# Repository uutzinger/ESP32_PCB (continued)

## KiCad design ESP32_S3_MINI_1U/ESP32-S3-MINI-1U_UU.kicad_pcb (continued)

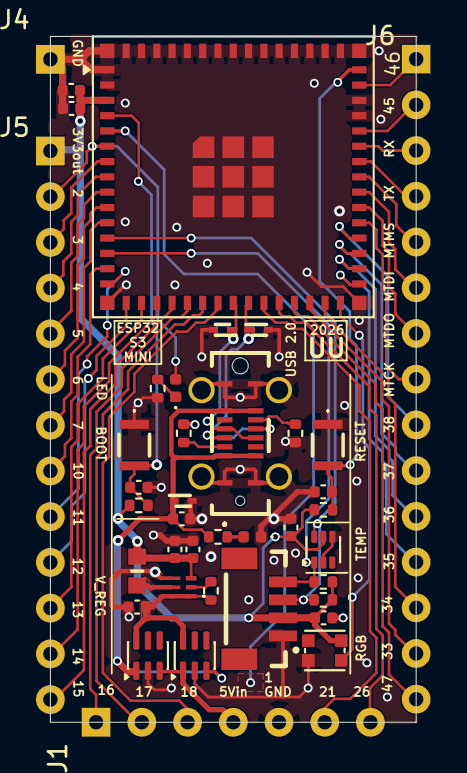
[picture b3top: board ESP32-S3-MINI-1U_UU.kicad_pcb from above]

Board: 2 copper layers, 20.3 x 38.1 mm, 39 parts (0 on the bottom side), 50 nets.

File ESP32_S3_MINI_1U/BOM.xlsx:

PCBWay BoM
Item # | *Designator | *Qty | Manufacturer | *Mfg Part # | Description / Value | Vendor Part # | *Package/Footprint | Category | Your Instructions / Notes | *Unit Price(5 sets) | *Total | *Delivery Time | *Actual Purchase Mfg Part # | *PCBWay Note | Customer Reply
1 | C11,C12,C10,C4 | 4 | muRata | GRM155R71A104KA01D | 0u1F | C71687 | C_0402_1005Metric | Capacitor | https://www.lcsc.com/product-detail/C71687.html?s_z=n_C71687 | 0.063 | 1.26
2 | C14 | 1 | YAGEO | CC0402KRX7R6BB103 | 10nF | C541371 | C_0402_1005Metric | Capacitor | https://www.lcsc.com/product-detail/C541371.html?s_z=n_C541371 | 0.126 | 0.63
3 | C3 | 1 | muRata | GRM158R61A226ME15D | 22uF | C3845593 | C_0402_1005Metric | Capacitor | https://www.lcsc.com/product-detail/C3845593.html?s_z=n_C3845593 | 0.263 | 1.315
4 | C5,C1,C2 | 3 | muRata | GRM155R61A106ME44D | 10uF | C77000 | C_0402_1005Metric | Capacitor | https://www.lcsc.com/product-detail/C77000.html?s_z=n_C77000 | 0.123 | 1.845
5 | C9 | 1 | muRata | GRM155R61A475KEAAD | 4u7F | C77004 | C_0402_1005Metric | Capacitor | https://www.lcsc.com/product-detail/C77004.html?s_z=n_C77004 | 0.158 | 0.79
6 | D1 | 1 | onSemi | ESD9B5.0ST5G | ESD9B5.0ST5G | C111566『 』863-ESD9B5.0ST5G | D_SOD-923 | V_USB ESD | https://www.lcsc.com/product-detail/C111566.html?s_z=n_C111566『 』https://www.mo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 | 0.212 | 1.06
7 | D4,D5 | 2 | Vishay | VLMB1500-GS08 | LED BLUE | C511042『 』78-VLMB1500-GS08 | LED_0402_1005Metric | LED | https://www.lcsc.com/product-detail/C511042.html?s_z=n_C511042『 』https://www.mo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 | 0.419 | 4.19
8 | D6 | 1 | Worldsemi | WS2812B-2020 | WS2812B | C965555 | WS2812_2020 | RGB LED | https://www.lcsc.com/product-detail/C965555.html?s_z=n_C965555 | 0.119 | 0.595
9 | D7,D8 | 2 | onSemi | ESD9101P2T5G | ESD9101P2T5G | C41348159『 』863-ESD9101P2T5G | D_SOD-923 | USB ESD | https://www.lcsc.com/product-detail/C41348159.html?s_z=n_ESD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 』https:/… | 0.066 | 0.66
10 | IC1 | 1 | Texas Instruments | TPS6282533DMQR | TPS6282533DMQR | C3189971『 』595-TPS6282533DMQR | TPS6282533DMQR | Volt Regulator | https://www.lcsc.com/product-detail/C3189971.html?s_z=n_C3189971『 』https://www.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 | 1.811 | 9.055
11 | J1 | 1 | Do No Populate | Do No Populate | Castellated_1x07 |  | Castellated_1x07_P2.54mm_D0.80mm | Connector |  |  |  |  |  | [DNP不要贴];
12 | J2 | 1 | GCT | USB4120-03-C | USB4120-03-C | C3445864『 』640-USB4120-03-C | USB412003C | Connector | https://www.lcsc.com/product-detail/C3445864.html?s_z=n_C3445864『 』https://www.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 | 1.642 | 8.21
13 | J3 | 1 | BOOMELE | 1.0T-4P | Qwiic_Vertical | C2974722 | JST_1x04_P1.0mm_Vertical_SMD | Connector | https://www.lcsc.com/product-detail/C2974722.html | 0.43 | 2.15 |  | 1.0T-4P卧贴编带
14 | J4 | 1 | Do No Populate | Do No Populate | Castellated_1x01 |  | Castellated_1x01_P2.54mm_D0.80mm | Connector |  |  |  |  |  | [DNP不要贴];
15 | J5 | 1 | Do No Populate | Do No Populate | Castellated_1x13 |  | Castellated_1x13_P2.54mm_D0.80mm | Connector |  |  |  |  |  | [DNP不要贴];
16 | J6 | 1 | Do No Populate | Do No Populate | Castellated_1x15 |  | Castellated_1x15_P2.54mm_D0.80mm | Connector |  |  |  |  |  | [DNP不要贴];
17 | L1 | 1 | TDK | TFM160808ALC-R47MTAA | TFM160808ALC-R47MTAA | C695609『 』810-TFM160808ALCR47A | INDC1608X75N | Inductor | https://www.lcsc.com/product-detail/C695609.html?s_z=n_C695609『 』https://www.mo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 | 0.357 | 1.785
18 | R1 | 1 | YAGEO | RC0402FR-07100KL | 100k | C60491 | R_0402_1005Metric | Resistor | https://www.lcsc.com/product-detail/C60491.html?s_z=n_C60491 | 0.032 | 0.16
19 | R12,R11 | 2 | YAGEO | RC0402FR-072K2L | 2k2 | C114762 | R_0402_1005Metric | Resistor | https://www.lcsc.com/product-detail/C114762.html?s_z=n_C114762 | 0.019 | 0.19
20 | R13,R17 | 2 | YAGEO | RC0402FR-0710KL | 10k | C60490 | R_0402_1005Metric | Resistor | https://www.lcsc.com/product-detail/C60490.html?s_z=n_C60490 | 0.019 | 0.19
21 | R14,R16 | 2 | YAGEO | RC0402FR-074K7L | 4k7 | C105871 | R_0402_1005Metric | Resistor | https://www.lcsc.com/product-detail/C105871.html?s_z=n_C105871 | 0.019 | 0.19
22 | R4,R5 | 2 | YAGEO | RC0402FR-075K1L | 5k1 | C105872 | R_0402_1005Metric | Resistor | https://www.lcsc.com/product-detail/C105872.html?s_z=n_C105872 | 0.019 | 0.19
23 | S1,S2 | 2 | C&K | NANOT160AS | NANOT160AS | C2760981『 』611-NANOT160AS | NANOT160AS | Micro Switch | https://www.lcsc.com/product-detail/C2760981.html?s_z=n_C2760981『 』https://www.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 | 0.686 | 6.86 | 7-10 Workdays
24 | U1 | 1 | Espressif Systems | ESP32-S3-MINI-1U-N8 | ESP32 S3 Mini 1U 8MB Flash | C2980299 | ESP32-S2-MINI-1U | MCU Module | https://www.lcsc.com/product-detail/C2980299.html?s_z=n_ESP3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 | 6.883 | 34.415 |  |  | The quoted part number is [ESP32-S3-MINI-1U-N8], not [ESP32-S2] as specified in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
25 | U2,U3 | 2 | Texas Instruments | LM66100DCK | Ideal Diode, Input Polarity Prot. | C2869734『 』595-LM66100DCKT | SOT-363_SC-70-6 | Ideal Diode | https://www.lcsc.com/product-detail/C2869734.html?s_z=n_C2869734『 』https://www.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 | 0.221 | 2.21
26 | U4 | 1 | Texas Instruments | TMP112AIDRLR | TMP112 | C28927 | SOT-563 | Temp Sensor | https://www.lcsc.com/product-image/C28927.html | 1.65 | 8.25
 |  |  |  |  |  |  |  |  |  | Component Cost | 86.2

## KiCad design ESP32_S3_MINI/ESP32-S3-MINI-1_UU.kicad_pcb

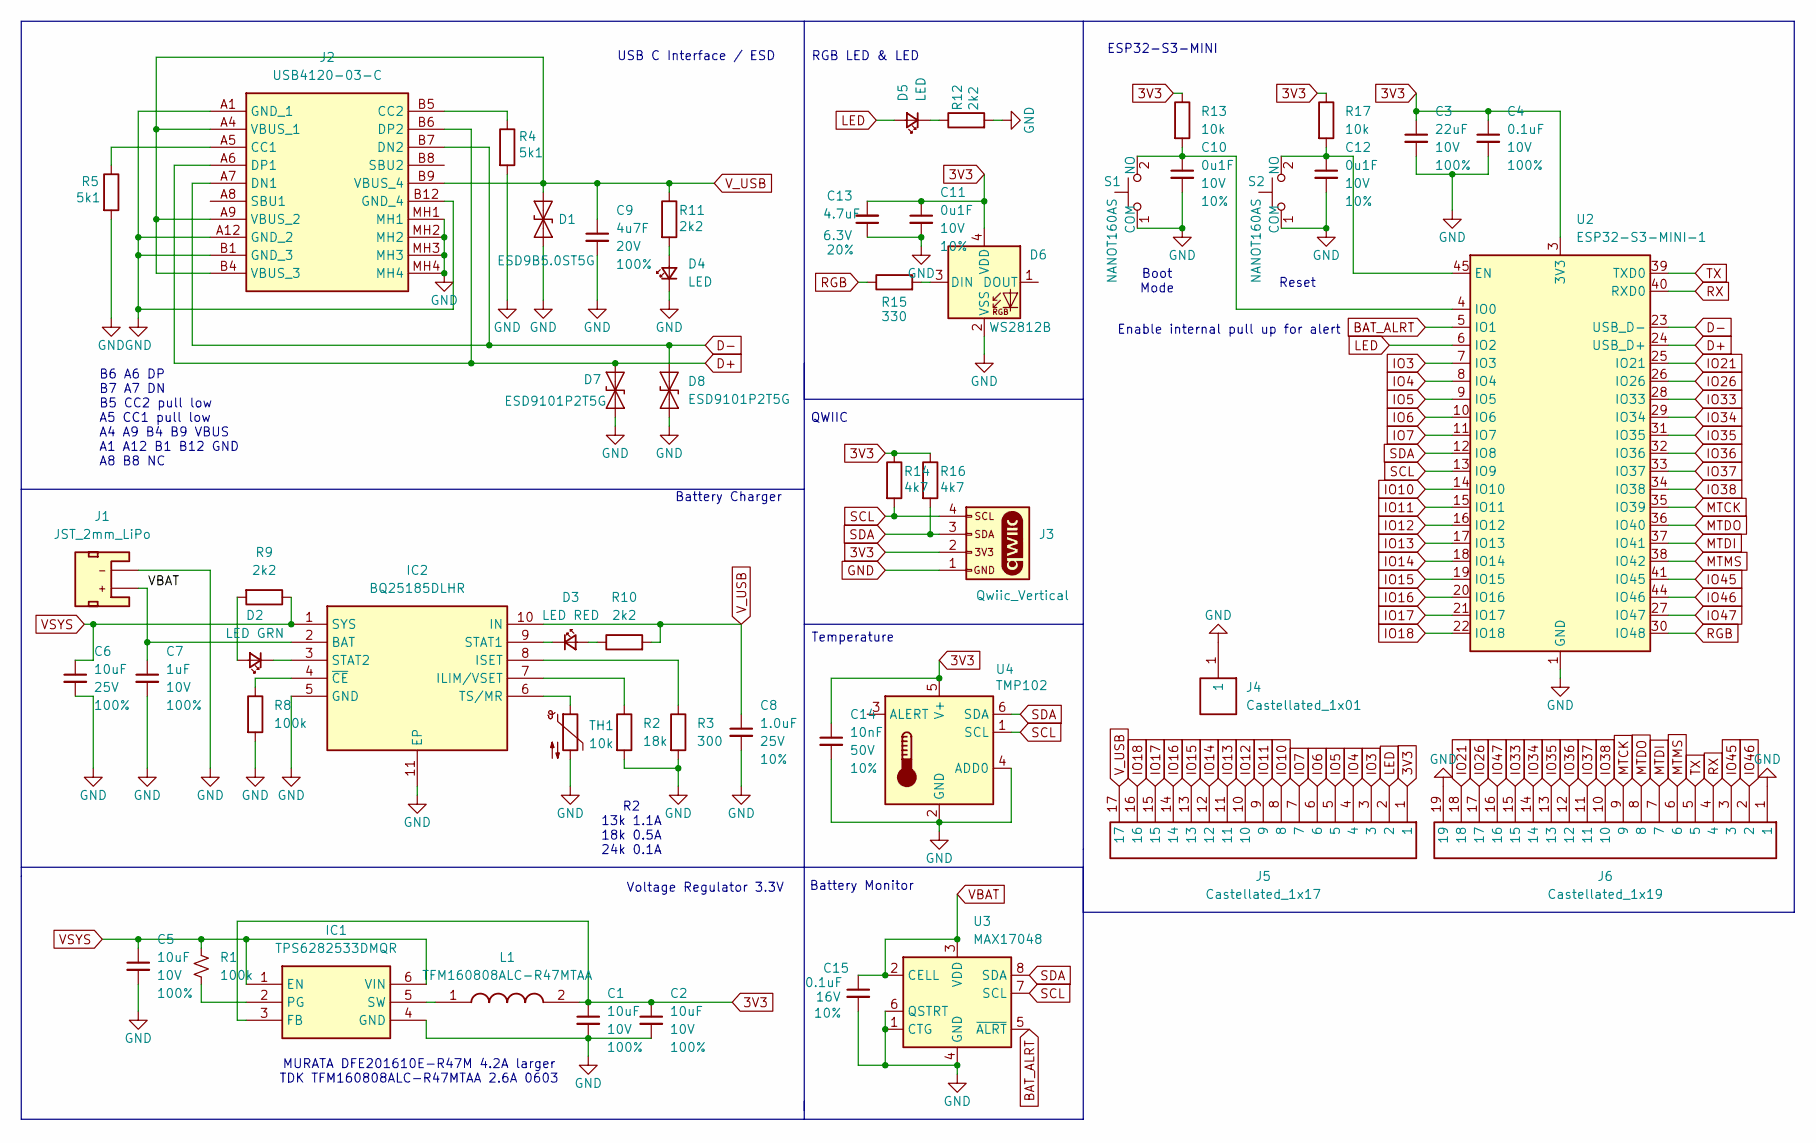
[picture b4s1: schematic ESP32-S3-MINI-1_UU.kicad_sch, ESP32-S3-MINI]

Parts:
C1, C2, C5: 10uF; C_0402_1005Metric; Voltage 10V; Tolerance 100%
C3: 22uF; C_0402_1005Metric; Voltage 10V; Tolerance 100%
C4: 0.1uF; C_0402_1005Metric; Voltage 10V; Tolerance 100%
C6: 10uF; C_0402_1005Metric; Voltage 25V; Tolerance 100%
C7: 1uF; C_0402_1005Metric; Voltage 10V; Tolerance 100%
C8: 1.0uF; C_0402_1005Metric; Voltage 25V; Tolerance 10%
C9: 4u7F; C_0402_1005Metric; Voltage 20V; Tolerance 100%
C10, C11, C12: 0u1F; C_0402_1005Metric; Voltage 10V; Tolerance 10%
C13: 4.7uF; C_0402_1005Metric; Voltage 6.3V; Tolerance 20%
C14: 10nF; C_0402_1005Metric; Voltage 50V; Tolerance 10%
C15: 0.1uF; C_0402_1005Metric; Voltage 16V; Tolerance 10%
D1: ESD9B5.0ST5G; D_SOD-923
D2: LED GRN; LED_0402_1005Metric
D3: LED RED; LED_0402_1005Metric
D4, D5: LED; LED_0402_1005Metric
D6: WS2812B; WS2812_2020
D7, D8: ESD9101P2T5G; D_SOD-923
IC1: TPS6282533DMQR; Manufacturer_Part_Number TPS6282533DMQR; Mouser Part Number 595-TPS6282533DMQR
IC2: BQ25185DLHR; SON40P220X200X80-11N; Manufacturer_Part_Number BQ25185DLHR; Mouser Part Number 595-BQ25185DLHR
J1: JST_2mm_LiPo; JST_1x02_P2.0mm_Horizontal_SMD
J2: USB4120-03-C; USB412003C; Manufacturer_Part_Number USB4120-03-C; Mouser Part Number 640-USB4120-03-C
J3: Qwiic_Vertical; JST_1x04_P1.0mm_Vertical_SMD
J4: Castellated_1x01; Castellated_1x01_P2.54mm_D0.80mm
J5: Castellated_1x17; Castellated_1x017_P2.54mm_D0.80mm
J6: Castellated_1x19; Castellated_1x019_P2.54mm_D0.80mm
L1: TFM160808ALC-R47MTAA; INDC1608X75N; Manufacturer_Part_Number TFM160808ALC-R47MTAA; Mouser Part Number 810-TFM160808ALCR47A
R1, R8: 100k; R_0402_1005Metric
R2: 18k; R_0402_1005Metric
R3: 300; R_0402_1005Metric
R4, R5: 5k1; R_0402_1005Metric
R9, R10, R11, R12: 2k2; R_0402_1005Metric
R13, R17: 10k; R_0402_1005Metric
R14, R16: 4k7; R_0402_1005Metric
R15: 330; R_0402_1005Metric
S1, S2: NANOT160AS; Mouser Part Number 611-NANOT160AS
TH1: 10k; R_0402_1005Metric
U2: ESP32-S3-MINI-1; ESP32-S2-MINI-1
U3: MAX17048; DFN-8_2x2mm_P0.5mm_EP1.2x0.8mm
U4: TMP102; SOT-563

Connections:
3V3: C1.1, C2.1, C3.1, C4.1, C11.1, C13.2, C14.1, D6.4 (VDD), IC1.3 (FB), J3.2, J5.1, L1.2, R13.1, R14.1, R16.1, R17.1, U2.3 (3V3), U4.5 (V+)
BAT_ALRT: U2.5 (IO1), U3.5 (~ALRT)
D+: D7.2 (A2), J2.A6 (DP1), J2.B6 (DP2), U2.24 (USB_D+)
D-: D8.2 (A2), J2.A7 (DN1), J2.B7 (DN2), U2.23 (USB_D-)
GND: C1.2, C2.2, C3.2, C4.2, C5.2, C6.2, C7.2, C8.2, C9.2, C10.2, C11.2, C12.2, C13.1, C14.2, C15.2, D1.1 (A1), D4.1 (K), D6.2 (VSS), D7.1 (A1), D8.1 (A1), IC1.4 (GND), IC2.5 (GND), IC2.11 (EP), J1.1 (-), J2.A1 (GND_1), J2.A12 (GND_2), J2.B1 (GND_3), J2.B12 (GND_4), J2.MH1, J2.MH2, J2.MH3, J2.MH4, J3.1, J4.1, J6.1, J6.19, R2.2, R3.2, R4.2, R5.2, R8.2, R12.2, S1.1 (COM), S2.1 (COM), TH1.2, U2.1 (GND), U2.2 (GND), U2.42 (GND), U2.43 (GND), U2.46 (GND), U2.47 (GND), U2.48 (GND), U2.49 (GND), U2.50 (GND), U2.51 (GND), U2.52 (GND), U2.53 (GND), U2.54 (GND), U2.55 (GND), U2.56 (GND), U2.57 (GND), U2.58 (GND), U2.59 (GND), U2.60 (GND), U2.61 (GND), U2.62 (GND), U2.63 (GND), U2.64 (GND), U2.65 (GND), U3.1 (CTG), U3.4 (GND), U3.6 (QSTRT), U3.9 (GND), U4.2 (GND), U4.4 (ADD0)
IO3: J5.3, U2.7 (IO3)
IO4: J5.4, U2.8 (IO4)
IO5: J5.5, U2.9 (IO5)
IO6: J5.6, U2.10 (IO6)
IO7: J5.7, U2.11 (IO7)
IO10: J5.8, U2.14 (IO10)
IO11: J5.9, U2.15 (IO11)
IO12: J5.10, U2.16 (IO12)
IO13: J5.11, U2.17 (IO13)
IO14: J5.12, U2.18 (IO14)
IO15: J5.13, U2.19 (IO15)
IO16: J5.14, U2.20 (IO16)
IO17: J5.15, U2.21 (IO17)
IO18: J5.16, U2.22 (IO18)
IO21: J6.18, U2.25 (IO21)
IO26: J6.17, U2.26 (IO26)
IO33: J6.15, U2.28 (IO33)
IO34: J6.14, U2.29 (IO34)
IO35: J6.13, U2.31 (IO35)
IO36: J6.12, U2.32 (IO36)
IO37: J6.11, U2.33 (IO37)
IO38: J6.10, U2.34 (IO38)
IO45: J6.3, U2.41 (IO45)
IO46: J6.2, U2.44 (IO46)
IO47: J6.16, U2.27 (IO47)
LED: D5.2 (A), J5.2, U2.6 (IO2)
MTCK: J6.9, U2.35 (IO39)
MTDI: J6.7, U2.37 (IO41)
MTDO: J6.8, U2.36 (IO40)
MTMS: J6.6, U2.38 (IO42)
unnamed: D2.2 (A), R9.2
unnamed: D2.1 (K), IC2.3 (STAT2)
unnamed: D3.2 (A), R10.1
unnamed: D3.1 (K), IC2.9 (STAT1)
unnamed: D4.2 (A), R11.2
unnamed: D5.1 (K), R12.1
unnamed: D6.3 (DIN), R15.2
unnamed: IC1.2 (PG), R1.1
unnamed: IC1.5 (SW), L1.1
unnamed: IC2.7 (ILIM/VSET), R2.1
unnamed: IC2.8 (ISET), R3.1
unnamed: IC2.6 (TS/MR), TH1.1
unnamed: IC2.4 (~CE), R8.1
unnamed: J2.A5 (CC1), R5.1
unnamed: J2.B5 (CC2), R4.1
unnamed: C10.1, R13.2, S1.2 (NO), U2.4 (IO0)
unnamed: C12.1, R17.2, S2.2 (NO), U2.45 (EN)
RGB: R15.1, U2.30 (IO48)
RX: J6.4, U2.40 (RXD0)
SCL: J3.4, R14.2, U2.13 (IO9), U3.7 (SCL), U4.1 (SCL)
SDA: J3.3, R16.2, U2.12 (IO8), U3.8 (SDA), U4.6 (SDA)
TX: J6.5, U2.39 (TXD0)
VBAT: C7.1, C15.1, IC2.2 (BAT), J1.2 (+), U3.2 (CELL), U3.3 (VDD)
VSYS: C5.1, C6.1, IC1.1 (EN), IC1.6 (VIN), IC2.1 (SYS), R1.2, R9.1
V_USB: C8.1, C9.1, D1.2 (A2), IC2.10 (IN), J2.A4 (VBUS_1), J2.A9 (VBUS_2), J2.B4 (VBUS_3), J2.B9 (VBUS_4), J5.17, R10.2, R11.1

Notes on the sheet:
Voltage Regulator 3.3V
Boot Mode
ESP32-S3-MINI
Battery Monitor
MURATA DFE201610E-R47M 4.2A larger TDK TFM160808ALC-R47MTAA 2.6A 0603
Temperature
RGB LED & LED
Reset
R2 13k 1.1A 18k 0.5A 24k 0.1A
Battery Charger
Enable internal pull up for alert
B6 A6 DP B7 A7 DN B5 CC2 pull low A5 CC1 pull low A4 A9 B4 B9 VBUS A1 A12 B1 B12 GND A8 B8 NC
USB C Interface / ESD
QWIIC

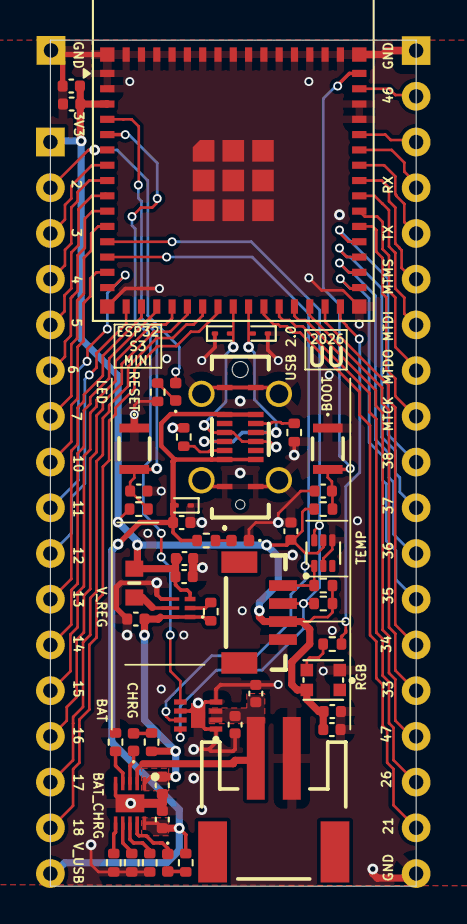
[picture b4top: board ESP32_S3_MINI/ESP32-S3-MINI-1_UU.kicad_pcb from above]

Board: 2 copper layers, 20.3 x 47.0 mm, 53 parts (0 on the bottom side), 60 nets.

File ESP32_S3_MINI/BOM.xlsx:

Id | Designator | Footprint | Quantity | Item | Manufacturer | Mfg Part # | Description/Value | Part # LCSC | Supplier and ref | LSCS $ | Part # Mouser | Mouser website | Mouser $ | Cost LCSC | Cost Mouser & LCSC
1 | C11,C12,C10,C15,C4 | C_0402_1005Metric | 5 | Capacitor | muRata | GRM155R71A104KA01D | 0u1F | C71687 | LCSC | 0.32 |  |  |  | 1.6 | 1.6
2 | C14 | C_0402_1005Metric | 1 | Capacitor | YAGEO | CC0402KRX7R6BB103 | 10nF | C541371 | LCSC | 0.13 |  |  |  | 0.13 | 0.13
3 | C3 | C_0402_1005Metric | 1 | Capacitor | muRata | GRM158R61A226ME15D | 22uF | C3845593 | LCSC | 0.57 |  |  |  | 0.57 | 0.57
4 | C5,C1,C2,C6 | C_0402_1005Metric | 4 | Capacitor | muRata | GRM155R61A106ME44D | 10uF | C77000 | LCSC | 0.58 |  |  |  | 2.32 | 2.32
5 | C7,C8 | C_0402_1005Metric | 2 | Capacitor | muRata | GCM155C71A105KE38D | 1uF | C126521 | LCSC | 0.96 |  |  |  | 1.92 | 1.92
6 | C9,C13 | C_0402_1005Metric | 2 | Capacitor | muRata | GRM155R61A475KEAAD | 4u7F | C77004 | LCSC | 0.81 |  |  |  | 1.62 | 1.62
7 | D1 | D_SOD-923 | 1 | V_USB ESD | onSemi | ESD9B5.0ST5G | ESD9B5.0ST5G | C111566 | LCSC | 0.04 | 863-ESD9B5.0ST5G | https://www.mouser.com/ProductDetail/onsemi/ESD9B5.0ST5G?qs=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 | 0.1 | 0.04 | 0.1
8 | D2 | LED_0402_1005Metric | 1 | LED | Vishay | VLMG1500-GS08 | LED GRN | C511404 | LCSC | 0.19 | 78-VLMG1500-GS08 | https://www.mouser.com/ProductDetail/Vishay-Semiconductors/V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 | 0.34 | 0.19 | 0.34
9 | D3 | LED_0402_1005Metric | 1 | LED | Vishay | VLMS1500-GS08 | LED RED | C511370 | LCSC | 0.17 | 78-VLMS1500-GS08 | https://www.mouser.com/ProductDetail/Vishay-Semiconductors/V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 | 0.24 | 0.17 | 0.24
10 | D4,D5 | LED_0402_1005Metric | 2 | LED | Vishay | VLMB1500-GS08 | LED BLUE | C511042 | LCSC | 0.2 | 78-VLMB1500-GS08 | https://www.mouser.com/ProductDetail/Vishay-Semiconductors/V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 | 0.27 | 0.4 | 0.54
11 | D6 | WS2812_2020 | 1 | RGB LED | Worldsemi | WS2812B-2020 | WS2812B | C965555 | LCSC | 0.45 |  |  |  | 0.45 | 0.45
12 | D7,D8 | D_SOD-923 | 2 | USB ESD | Onsemi | ESD9101P2T5G | ESD9101P2T5G | C41348159 | LCSC | 0.56 | 863-ESD9101P2T5G | https://www.mouser.com/ProductDetail/onsemi/ESD9101P2T5G?qs=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 | 0.26 | 1.12 | 0.52
13 | IC1 | TPS6282533DMQR | 1 | Volt Regulator | TI | TPS6282533DMQR | TPS6282533DMQR | C3189971 | LCSC | 1.17 | 595-TPS6282533DMQR | https://www.mouser.com/ProductDetail/Texas-Instruments/TPS62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 | 1.25 | 1.17 | 1.25
14 | IC2 | SON40P220X200X80-11N | 1 | Bat Charger | TI | BQ25185DLHR | BQ25185DLHR | C19725033 | LCSC | 1.9 | 595-BQ25185DLHR | https://www.mouser.com/ProductDetail/Texas-Instruments/BQ251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 | 2.03 | 1.9 | 2.03
15 | J1 | JST_1x02_P2.0mm_Horizontal_SMD | 1 | Connector | JST | JST S2B-PH-SM4-TB | JST_2mm_LiPo, SMF, right angle | C295747 | LCSC | 0.2 | 306-S2BPHSM4TBLFSN | https://www.mouser.com/ProductDetail/JST-Commercial/S2B-PH-S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 | 0.49 | 0.2 | 0.49
16 | J2 | USB412003C | 1 | Connector | GCT | USB4120-03-C | USB4120-03-C | C3445864 | LCSC | 1.31 | 640-USB4120-03-C | https://www.mouser.com/ProductDetail/GCT/USB4120-03-C?qs=KUo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 | 0.86 | 1.31 | 0.86
17 | J3 | JST_1x04_P1.0mm_Vertical_SMD | 1 | Connector | BOOMELE | 1.0T-4P | Qwiic_Vertical | C970137 | LCSC | 0.65 |  |  |  | 0.65 | 0.65
18 | J4 | Castellated_1x01_P2.54mm_D0.80mm | 1 | Connector | D.N.P. | D.N.P. | Castellated_1x01 |  | Do No Populate |  |  |  |  | 0 | 0
19 | J5 | Castellated_1x017_P2.54mm_D0.80mm | 1 | Connector | D.N.P. | D.N.P. | Castellated_1x17 |  | Do No Populate |  |  |  |  | 0 | 0
20 | J6 | Castellated_1x019_P2.54mm_D0.80mm | 1 | Connector | D.N.P. | D.N.P. | Castellated_1x19 |  | Do No Populate |  |  |  |  | 0 | 0
21 | L1 | C_0603 | 1 | Inductor | TDK | TFM160808ALC-R47MTAA | TFM160808ALC-R47MTAA | C695609 | LCSC | 0.13 | 810-TFM160808ALCR47A | https://www.mouser.com/ProductDetail/TDK/TFM160808ALC-R47MTA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 | 0.25 | 0.13 | 0.25
22 | R1,R8 | R_0402_1005Metric | 2 | Resistor | YAGEO | RC0402FR-07100KL | 100k | C60491 | LCSC | 0.08 |  |  |  | 0.16 | 0.16
23 | R14,R16 | R_0402_1005Metric | 2 | Resistor | YAGEO | RC0402FR-074K7L | 4k7 | C105871 | LCSC | 0.08 |  |  |  | 0.16 | 0.16
24 | R15 | R_0402_1005Metric | 1 | Resistor | YAGEO | RC0402FR-07330RL | 330 | C105875 | LCSC | 0.08 |  |  |  | 0.08 | 0.08
25 | R2 | R_0402_1005Metric | 1 | Resistor | YAGEO | RC0402FR-0718KL | 18k | C138044 | LCSC | 0.08 |  |  |  | 0.08 | 0.08
26 | R3 | R_0402_1005Metric | 1 | Resistor | YAGEO | RC0402FR-07300RL | 300 | C138010 | LCSC | 0.08 |  |  |  | 0.08 | 0.08
27 | R4,R5 | R_0402_1005Metric | 2 | Resistor | YAGEO | RC0402FR-075K1L | 5k1 | C105872 | LCSC | 0.08 |  |  |  | 0.16 | 0.16
28 | R9,R12,R10,R11 | R_0402_1005Metric | 4 | Resistor | YAGEO | RC0402FR-072K2L | 2k2 | C114762 | LCSC | 0.09 |  |  |  | 0.36 | 0.36
29 | S1,S2 | NANOT160AS | 2 | Micro Switch | C&K | NANOT160AS | NANOT160AS | C2760981 | LCSC | 1.72 | 611-NANOT160AS | https://www.mouser.com/ProductDetail/CK/NANOT160AS?qs=OlC7Aq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 | 0.4 | 3.44 | 0.8
30 | R13,R17 | R_0402_1005Metric | 2 | Resistor | YAGEO | RC0402FR-0710KL | 10k | C60490 | LCSC | 0.08 |  |  |  | 0.16 | 0.16
31 | TH1 | R_0402_1005Metric | 1 | Thermistor | MURATA | NCP15XH103F03RC | 10k NTC | C77131 | LCSC | 0.01 |  |  |  | 0.01 | 0.01
32 | U2 | ESP32-S2-MINI-1 SMD | 1 | MCU Module | Espressif | ESP32-S3-MINI-1-N8 | ESP32 S3 Mini 1 8MB Flash | C2913206 | LCSC | 4.6185 |  |  |  | 4.6185 | 4.6185
33 | U3 | DFN-8_2x2mm_P0.5mm_EP1.2x0.8mm | 1 | Bat Gauge | Maxim | MAXIM MAX17048G+T10 | MAX17048 | C2682616 | LCSC | 2.66 | 700-MAX17048G+T10 | https://www.mouser.com/ProductDetail/Analog-Devices-Maxim-In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 | 5.77 | 2.66 | 5.77
34 | U4 | SOT-563 | 1 | Temp Sensor | Texas Instruments | TMP102AIDRLR | TMP102 | C99269 | LCSC | 0.22 | 595-TMP102AQDRLRQ1 | https://www.mouser.com/ProductDetail/Texas-Instruments/TMP10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 | 1.52 | 0.22 | 1.52
 |  |  |  |  |  |  |  |  |  |  |  |  |  | 28.0785 | 29.8385

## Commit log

2026-02-09 Add section for ESP32-S3-MINI to README
2026-02-09 First Release
2026-02-09 Design Review
2026-02-09 Side View
2026-02-09 3D updates
2026-02-10 Cleanup
2026-02-10 Labels
2026-02-15 1U module release
2026-02-15 Adjust image width for ESP32-S3-MINI-1
    Reduced image width for ESP32-S3-MINI-1 in README.
2026-02-15 Adjust image width and improve text formatting
    Updated image width and formatted description text.
2026-02-15 reorganized folders
2026-02-15 Improve README table layout and formatting
    Updated table layout and fixed formatting issues.
2026-02-15 Fix formatting in README.md
2026-02-15 image scaling
2026-02-15 Improve README table formatting and image styles
    Updated the HTML structure and styling for better formatting.
2026-02-15 Description
2026-02-15 remove backups
2026-02-16 ESP32-S3-1 updates from 1U design
2026-02-16 S3-1 3d pic update
2026-02-16 Readme update
2026-02-16 Minor update
2026-02-16 BOM update
2026-02-16 Silk update
2026-02-16 Sync Update
2026-02-17 Trace cleanup
2026-02-26 Differential USB routing
2026-06-03 Update ESP32 PCB projects and generated assets
2026-06-03 Add ESP32-S3-MINI-1U Arduino folder and ignore KiCad backups
2026-06-03 Fix markdown document links and ignore KiCad lock files
2026-06-03 Update README module description
